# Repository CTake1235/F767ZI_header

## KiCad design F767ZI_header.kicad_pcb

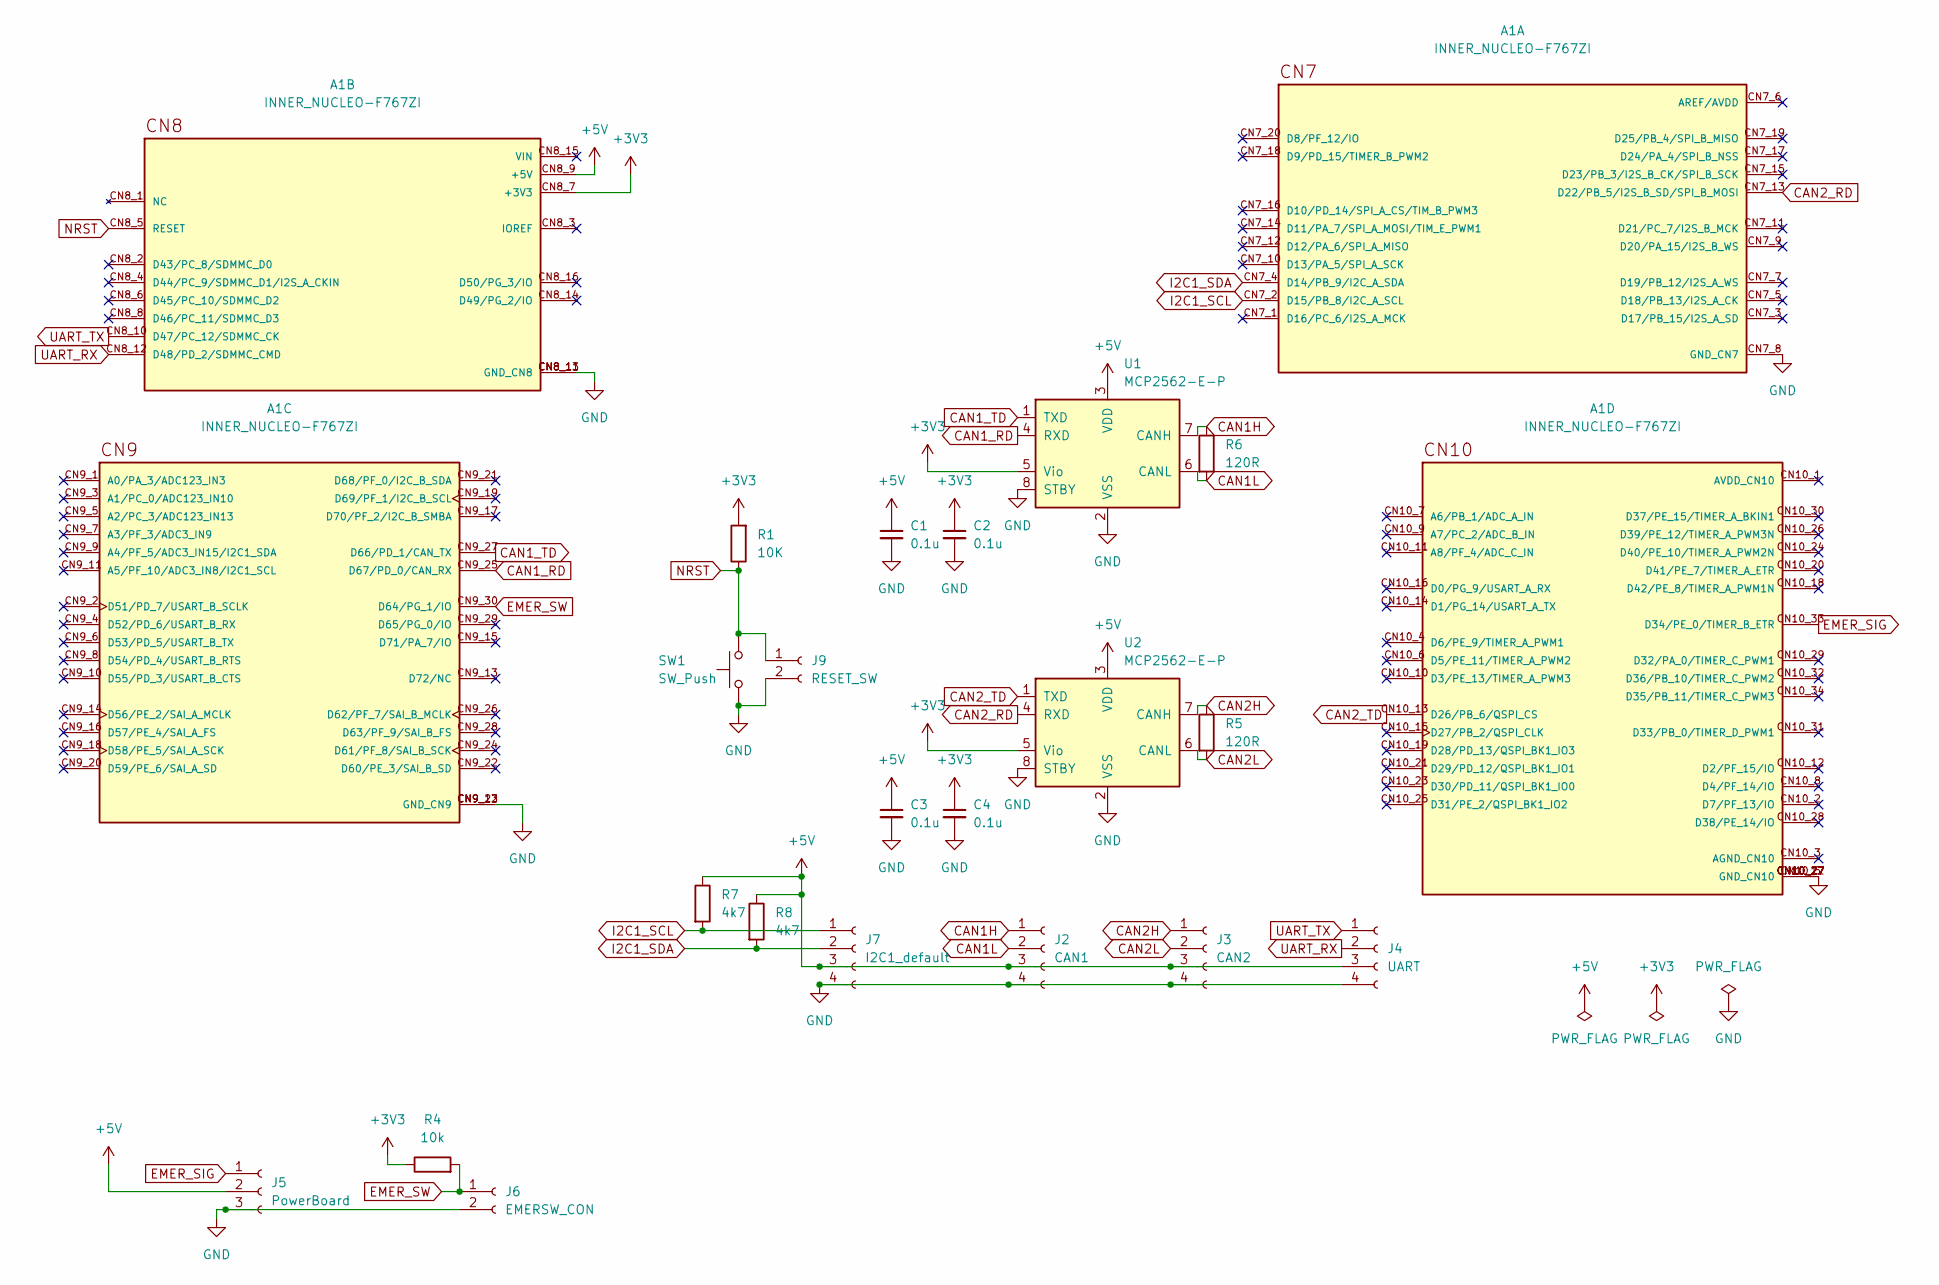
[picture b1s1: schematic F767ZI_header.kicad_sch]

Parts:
A1: INNER_NUCLEO-F767ZI; INNER_ST_NUCLEO-F767ZI; PARTREV 7
C1, C2, C3, C4: 0.1u; C_Disc_D5.0mm_W2.5mm_P2.50mm
J2: CAN1; JST_XA_B04B-XASK-1_1x04_P2.50mm_Vertical
J3: CAN2; JST_XA_B04B-XASK-1_1x04_P2.50mm_Vertical
J4: UART; JST_XA_B04B-XASK-1_1x04_P2.50mm_Vertical
J5: PowerBoard; JST_XA_B03B-XASK-1_1x03_P2.50mm_Vertical
J6: EMERSW_CON; JST_XA_B02B-XASK-1_1x02_P2.50mm_Vertical
J7: I2C1_default; JST_XA_B04B-XASK-1_1x04_P2.50mm_Vertical
J9: RESET_SW; JST_XA_B02B-XASK-1_1x02_P2.50mm_Vertical
R1: 10K; R_Axial_DIN0207_L6.3mm_D2.5mm_P7.62mm_Horizontal
R4: 10k; R_Axial_DIN0207_L6.3mm_D2.5mm_P7.62mm_Horizontal
R5, R6: 120R; R_Axial_DIN0207_L6.3mm_D2.5mm_P7.62mm_Horizontal
R7, R8: 4k7; R_Axial_DIN0207_L6.3mm_D2.5mm_P7.62mm_Horizontal
SW1: SW_Push; SW_PUSH_6mm
U1, U2: MCP2562-E-P; DIP-8_W7.62mm

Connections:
+3V3: A1.CN8_7 (+3V3), C2.1, C4.1, R1.2, R4.1, U1.5 (Vio), U2.5 (Vio)
+5V: A1.CN8_9 (+5V), C1.1, C3.1, J2.3, J3.3, J4.3, J5.2, J7.3, R7.1, R8.1, U1.3 (VDD), U2.3 (VDD)
CAN1H: J2.1, R6.1, U1.7 (CANH)
CAN1L: J2.2, R6.2, U1.6 (CANL)
CAN1_RD: A1.CN9_25 (D67/PD_0/CAN_RX), U1.4 (RXD)
CAN1_TD: A1.CN9_27 (D66/PD_1/CAN_TX), U1.1 (TXD)
CAN2H: J3.1, R5.1, U2.7 (CANH)
CAN2L: J3.2, R5.2, U2.6 (CANL)
CAN2_RD: A1.CN7_13 (D22/PB_5/I2S_B_SD/SPI_B_MOSI), U2.4 (RXD)
CAN2_TD: A1.CN10_13 (D26/PB_6/QSPI_CS), U2.1 (TXD)
EMER_SIG: A1.CN10_33 (D34/PE_0/TIMER_B_ETR), J5.1
EMER_SW: A1.CN9_30 (D64/PG_1/IO), J6.1, R4.2
GND: A1.CN7_8 (GND_CN7), A1.CN8_11 (GND_CN8), A1.CN8_13 (GND_CN8), A1.CN9_12 (GND_CN9), A1.CN9_23 (GND_CN9), A1.CN10_5 (GND_CN10), A1.CN10_17 (GND_CN10), A1.CN10_22 (GND_CN10), A1.CN10_27 (GND_CN10), C1.2, C2.2, C3.2, C4.2, J2.4, J3.4, J4.4, J5.3, J6.2, J7.4, J9.2, SW1.1, U1.2 (VSS), U1.8 (STBY), U2.2 (VSS), U2.8 (STBY)
I2C1_SCL: A1.CN7_2 (D15/PB_8/I2C_A_SCL), J7.1, R7.2
I2C1_SDA: A1.CN7_4 (D14/PB_9/I2C_A_SDA), J7.2, R8.2
NRST: A1.CN8_5 (RESET), J9.1, R1.1, SW1.2
UART_RX: A1.CN8_12 (D48/PD_2/SDMMC_CMD), J4.2
UART_TX: A1.CN8_10 (D47/PC_12/SDMMC_CK), J4.1

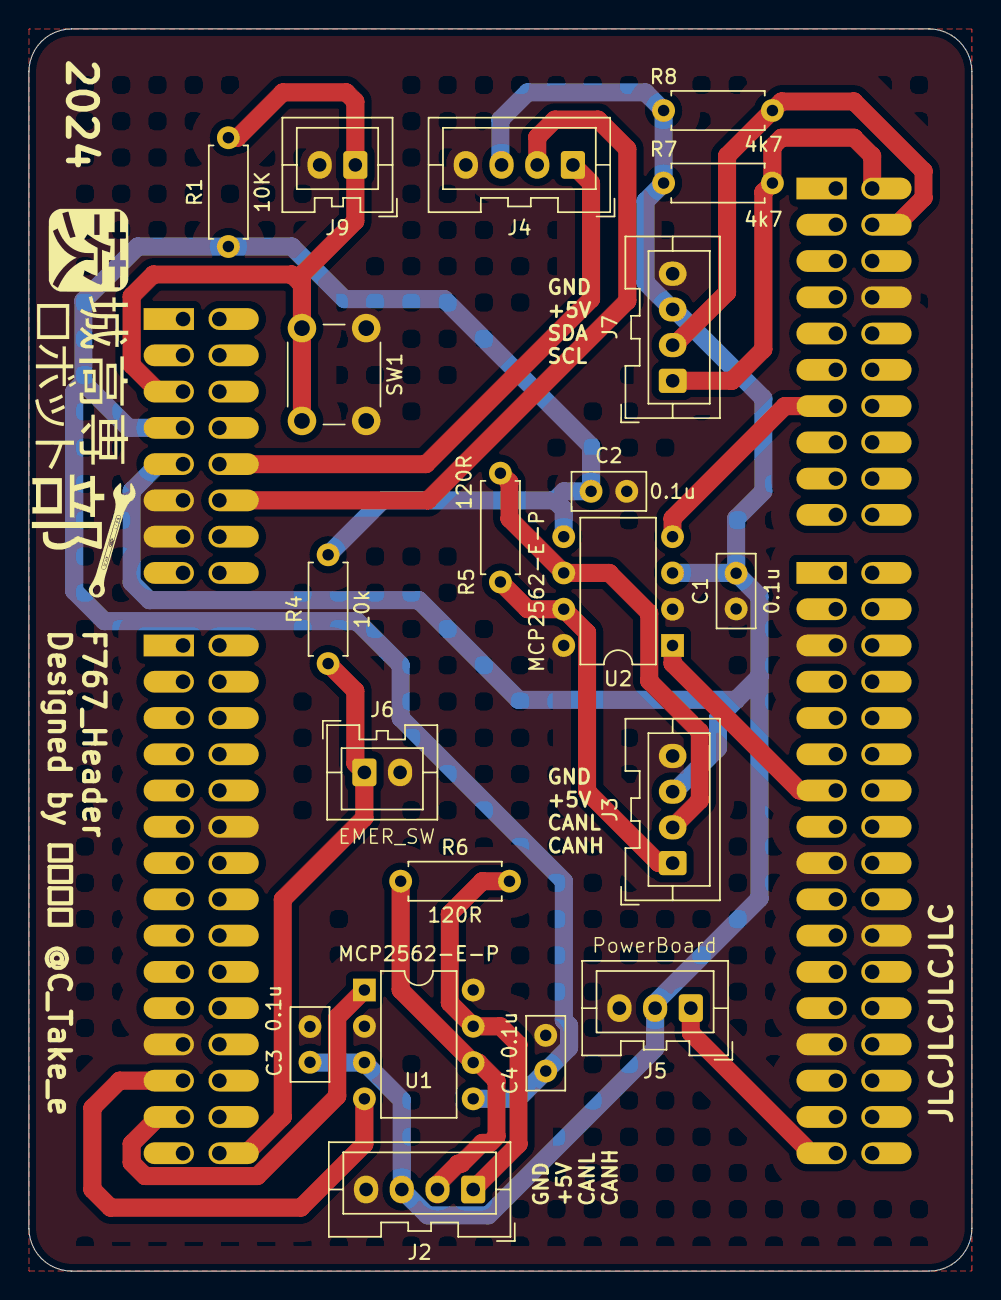
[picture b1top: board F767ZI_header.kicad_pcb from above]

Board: 2 copper layers, 66.0 x 87.0 mm, 21 parts (0 on the bottom side), 18 nets.

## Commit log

2024-04-15 sch: Add a CAN connector
2024-04-15 NEW: Create PinMap.xlsx
2024-04-15 gitignore: Ignore temporary file of xlsx
2024-04-15 SCH: add an I2C to use IMU & add C around MCP2562
2024-04-15 SCH: Replace pull-up of NRST
2024-04-15 SCH: Add CN8_1 to NUCLEO lib
2024-04-15 PCB: Update with SCH
2024-04-15 SCH&PCB: Fix NUCLEO ilb
2024-04-15 SCH: Connected GND & all transmission PINs
2024-04-15 PCB: Wired up all
2024-04-15 PCB: Place Connectors around the perimeter
2024-04-16 PCB: 詳細なシルクを追加
2024-04-16 MAP: 誤入力消去
2024-04-16 PCB: 発注用のシルクとロゴを追加
2024-04-17 SCH: I2C(MD)を削除
2024-04-17 PCB: 外形調整
2024-04-17 PCB: 外形縮小マン
2024-04-17 PDF: sch更新、pcb追加
2024-04-17 MAP: I2C(MD)の削除に対応
2024-04-17 PCB: 永久配置調整タイム
2024-04-17 MAP: 回路図と同期
2024-04-17 PCB: 外形のフィレット
2024-04-17 GBR: 全ガーバー出力
2024-04-17 MAP: シートの外形お手入れ、pdf印刷
2024-04-17 PCB/SCH: EMER_SIGのピン変更、コネクタ再配置
2024-04-17 MAP: ピン配更新
2024-04-17 PCB: 部品密度こそ正義
2024-04-17 PCB: 寸法線追加、外形フィレット
2024-04-17 PCB/SCH: PDF更新
2024-04-17 GBR: 全部出し
2024-05-13 SCH: トランシーバのSTBYをGNDに接続
2024-05-13 PCB: トランシーバのSTBYピンをGNDに接続
2024-05-13 PDF: 更新
2024-05-13 GBR: 全部出し直し
